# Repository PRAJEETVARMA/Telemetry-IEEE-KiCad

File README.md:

# Telemetry-IEEE-KiCad
Design a telemetry system using BMP280, DHT11, MPU6050, NEO-6M sensors
# Telemetry System Design using KiCad

## Project Overview
This project presents the schematic design of a telemetry system that collects
environmental, motion, and location data using multiple sensors.

## Components Used
- Arduino UNO
- BMP280 – Pressure and Temperature Sensor
- DHT11 – Temperature and Humidity Sensor
- MPU6050 – Accelerometer
- NEO-6M – GPS Module

## Communication Interfaces
- I²C: BMP280, MPU6050
- Digital GPIO: DHT11
- UART (D0, D1): NEO-6M GPS

## System Architecture
Sensors are interfaced with the Arduino UNO, which acts as the central controller.
The collected telemetry data is transmitted via serial communication to an
external system for logging and analysis.

## Design Tool
- KiCad (Schematic Design)

## Author
Prajeet Varma Mudunuri

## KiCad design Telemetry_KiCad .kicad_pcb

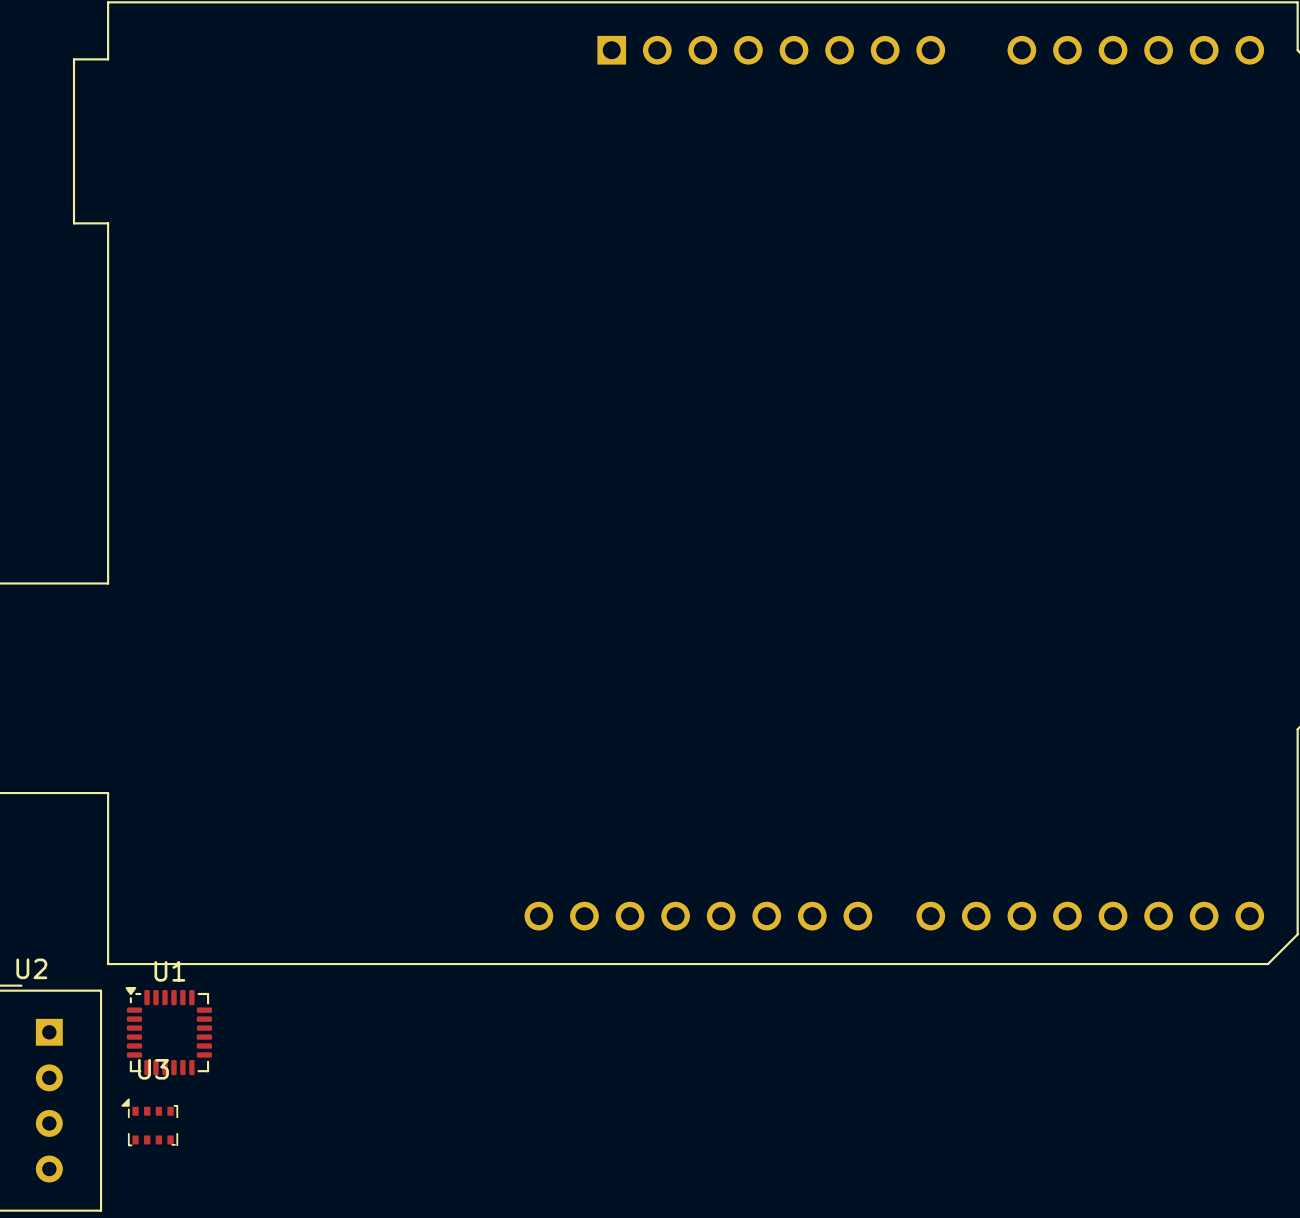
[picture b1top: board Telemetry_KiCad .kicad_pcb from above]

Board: 2 copper layers, 4 parts (0 on the bottom side), 3 nets, no tracks yet.

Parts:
A1: Arduino_UNO_R2
U1: MPU-6050; InvenSense_QFN-24_4x4mm_P0.5mm
U2: DHT11; Aosong_DHT11_5.5x12.0_P2.54mm
U3: BMP280; Bosch_LGA-8_2x2.5mm_P0.65mm_ClockwisePinNumbering

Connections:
+3.3V: U1.8 (VLOGIC), U1.13 (VDD), U1.18 (GND), U2.1 (VDD), U2.4 (GND), U3.1 (GND), U3.6 (VDDIO), U3.7 (GND), U3.8 (VDD)
unnamed: A1.14 (SCL/A5), U1.23 (SCL), U3.4 (SCK)
unnamed: A1.13 (SDA/A4), U1.24 (SDA), U3.3 (SDI)
